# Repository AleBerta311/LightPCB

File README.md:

This PCB uses USB voltage to control a sensor that turns light on when its dark.
The switch and debug pins are used to transfer the code for the microprocessor which controls the sensor and turns on/off the light.

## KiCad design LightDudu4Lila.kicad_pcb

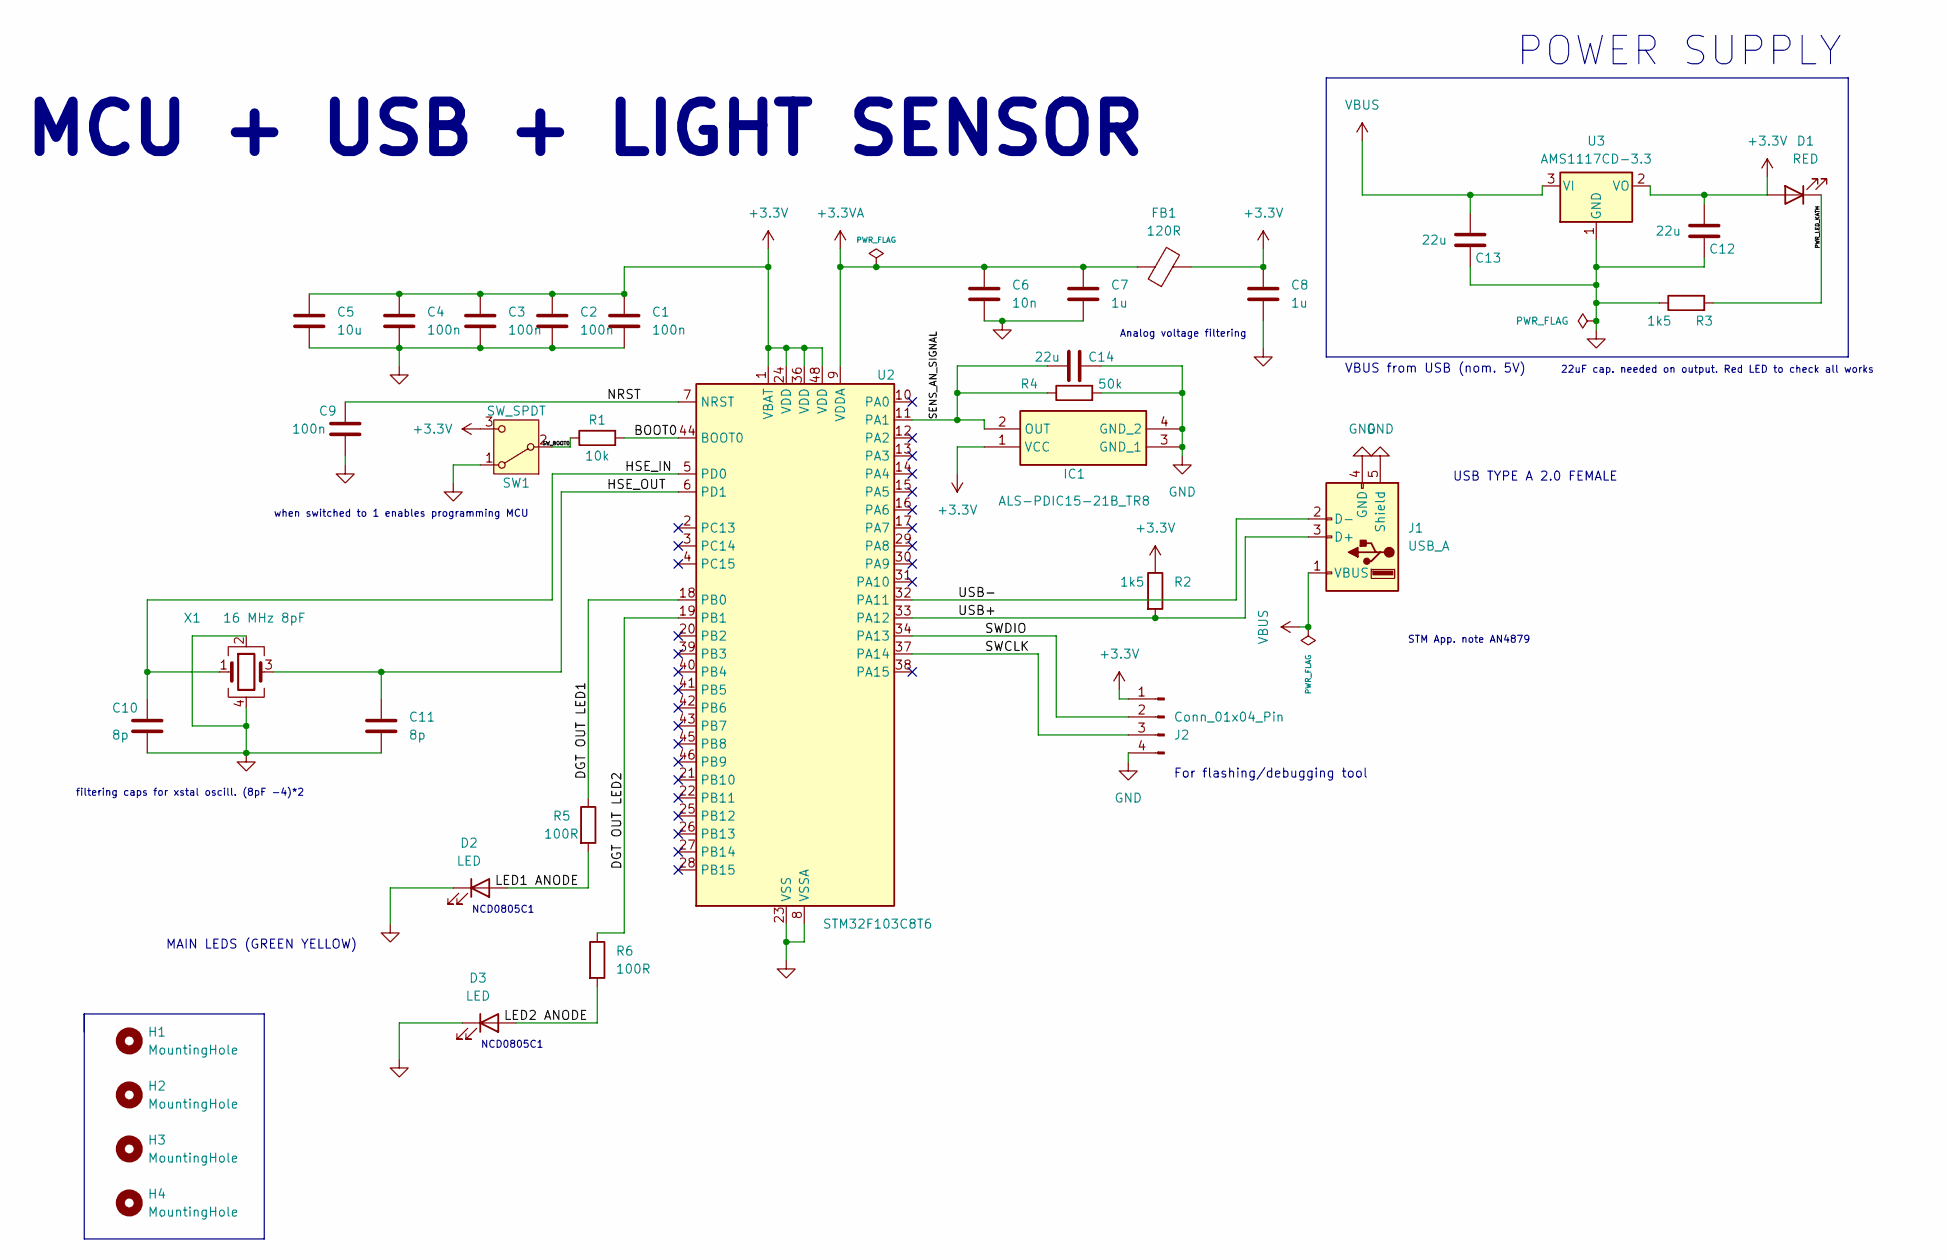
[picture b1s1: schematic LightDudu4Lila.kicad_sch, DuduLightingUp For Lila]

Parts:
C1, C2, C3, C4, C9: 100n; C_0402_1005Metric
C5: 10u; C_0603_1608Metric
C6: 10n; C_0402_1005Metric
C7, C8: 1u; C_0603_1608Metric
C10, C11: 8p; C_0402_1005Metric
C12, C13, C14: 22u; C_0805_2012Metric
D1: RED; LED_0603_1608Metric
D2, D3: LED; LED_0805_2012Metric
FB1: 120R; L_0603_1608Metric
H1, H2, H3, H4: MountingHole; MountingHole_2.2mm_M2
IC1: ALS-PDIC15-21B_TR8; ALSPDIC1521BTR8; Manufacturer_Part_Number ALS-PDIC15-21B/TR8
J1: USB_A; USB_A_Molex_67643_Horizontal
J2: Conn_01x04_Pin; FanPinHeader_1x04_P2.54mm_Vertical
R1: 10k; R_0402_1005Metric
R2, R3: 1k5; R_0402_1005Metric
R4: 50k; R_0805_2012Metric
R5, R6: 100R; R_1206_3216Metric
SW1: SW_SPDT; SW_E-Switch_EG1224_SPDT_Angled
U2: STM32F103C8T6; LQFP-48_7x7mm_P0.5mm
U3: AMS1117CD-3.3; TO-252-3_TabPin2
X1: 16 MHz 8pF; Crystal_SMD_3225-4Pin_3.2x2.5mm

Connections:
+3.3V: C1.1, C2.1, C3.1, C4.1, C5.1, C8.1, C12.1, D1.2 (A), FB1.2, IC1.1 (VCC), J2.1, R2.1, SW1.3 (C), U2.1 (VBAT), U2.24 (VDD), U2.36 (VDD), U2.48 (VDD), U3.2 (VO)
+3.3VA: C6.1, C7.1, FB1.1, U2.9 (VDDA)
/BOOT0: R1.2, U2.44 (BOOT0)
/DGT OUT LED1: R5.1, U2.18 (PB0)
/DGT OUT LED2: R6.1, U2.19 (PB1)
/HSE_IN: C10.1, U2.5 (PD0), X1.1
/HSE_OUT: C11.1, U2.6 (PD1), X1.3
/LED1 ANODE: D2.2 (A), R5.2
/LED2 ANODE: D3.2 (A), R6.2
/NRST: C9.1, U2.7 (NRST)
/PWR_LED_KATH: D1.1 (K), R3.2
/SENS_AN_SIGNAL: C14.1, IC1.2 (OUT), R4.1, U2.11 (PA1)
/SWCLK: J2.3, U2.37 (PA14)
/SWDIO: J2.2, U2.34 (PA13)
/SW_BOOT0: R1.1, SW1.2 (B)
/USB+: J1.3 (D+), R2.2, U2.33 (PA12)
/USB-: J1.2 (D-), U2.32 (PA11)
GND: C1.2, C2.2, C3.2, C4.2, C5.2, C6.2, C7.2, C8.2, C9.2, C10.2, C11.2, C12.2, C13.2, C14.2, D2.1 (K), D3.1 (K), IC1.3 (GND_1), IC1.4 (GND_2), J1.4 (GND), J1.5 (Shield), J2.4, R3.1, R4.2, SW1.1 (A), U2.8 (VSSA), U2.23 (VSS), U2.35 (VSS), U2.47 (VSS), U3.1 (GND), X1.2, X1.4
VBUS: C13.1, J1.1 (VBUS), U3.3 (VI)

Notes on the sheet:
For flashing/debugging tool
VBUS from USB (nom. 5V)
POWER SUPPLY
USB TYPE A 2.0 FEMALE
NCD0805C1
when switched to 1 enables programming MCU
22uF cap. needed on output. Red LED to check all works
filtering caps for xstal oscill. (8pF -4)*2
MCU + USB + LIGHT SENSOR
STM App. note AN4879
MAIN LEDS (GREEN YELLOW)
Analog voltage filtering

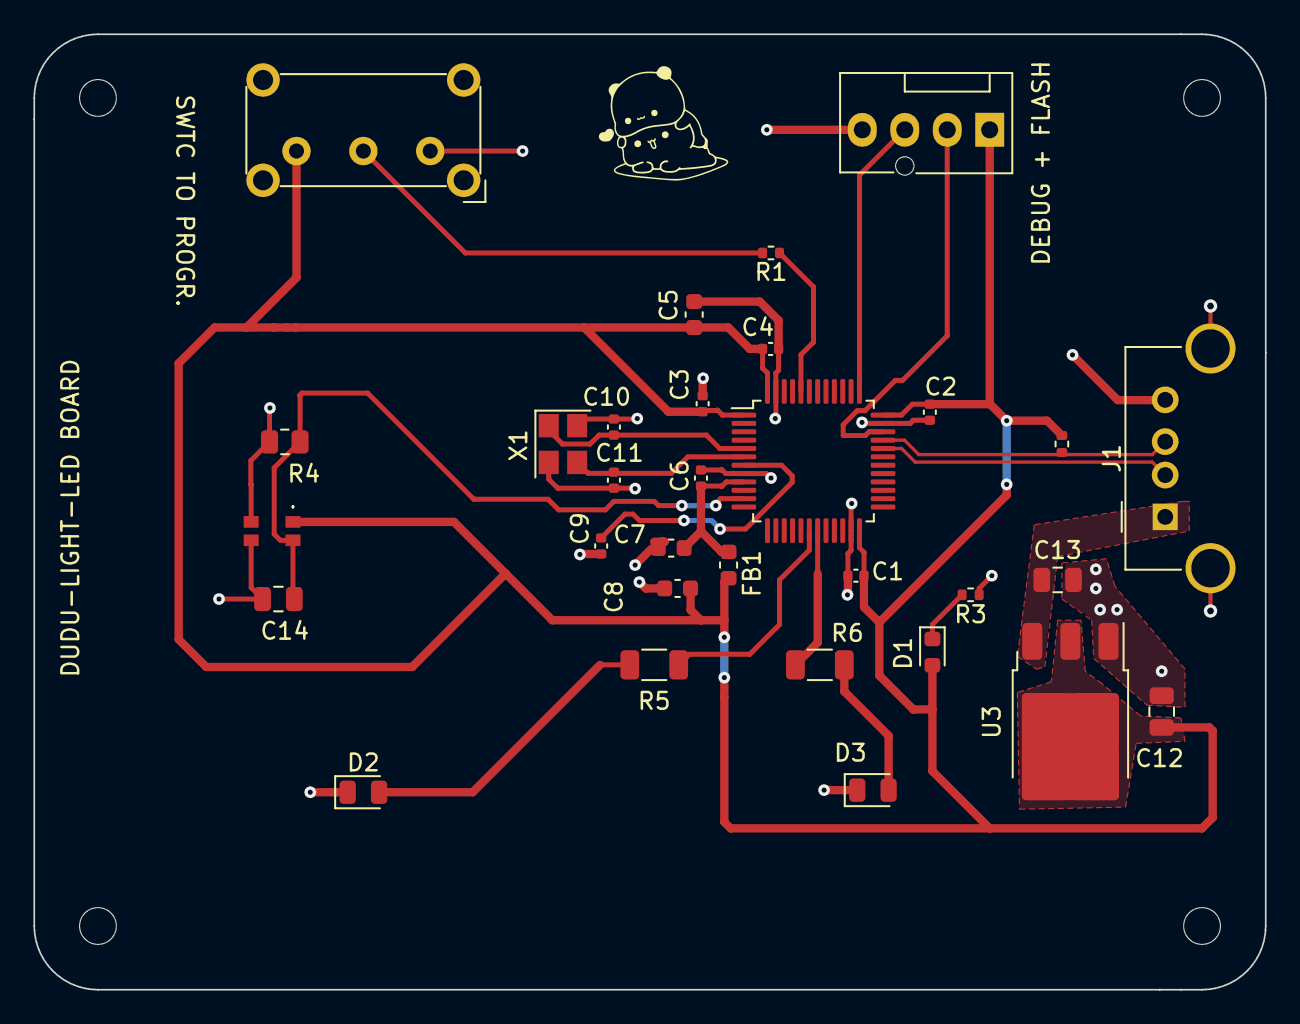
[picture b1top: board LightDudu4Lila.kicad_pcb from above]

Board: 2 copper layers, 73.7 x 57.1 mm, 35 parts (0 on the bottom side), 19 nets.

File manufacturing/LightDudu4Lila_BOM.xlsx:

Designator | Qnty | Comment | Cmp type | Footprint | Description | JLCPCB Part #
C1, C2, C3, C4, C9 | 5 | 100n | C | Capacitor_SMD:C_0402_1005Metric | Unpolarized capacitor | C694490
C5 | 1 | 10u | C | Capacitor_SMD:C_0603_1608Metric | Unpolarized capacitor | C385036
C6 | 1 | 10n | C | Capacitor_SMD:C_0402_1005Metric | Unpolarized capacitor | C342982
C7, C8 | 2 | 1u | C | Capacitor_SMD:C_0603_1608Metric | Unpolarized capacitor | C162280
C10, C11 | 2 | 8p | C | Capacitor_SMD:C_0402_1005Metric | Unpolarized capacitor | C1864375
C12, C13, C14 | 3 | 22u | C | Capacitor_SMD:C_0805_2012Metric | Unpolarized capacitor | C76634
D1 | 1 | red | LED | LED_SMD:LED_0603_1608Metric | Light emitting diode | C2286
D2, D3 | 2 | NCD0805C1 | LED | LED_SMD:LED_0805_2012Metric | Light emitting diode | C84257
FB1 | 1 | 120R @ 1 GHz | FerriteBead | Inductor_SMD:L_0603_1608Metric | Ferrite bead | C127301
IC1 | 1 | ALS-PDIC15-21B_TR8 | ALS-PDIC15-21B_TR8 | 1206 | SENSOR OPT 580NM AMBIENT SMD | C131243
J1 | 1 | 67643-3911 | USB_A | Connector_USB:USB_A_Molex_67643_Horizontal | USB Type A connector | C2765194
J2 | 1 | 01x04 pins connector | Conn_01x04_Pins | Connector:FanPinHeader_1x04_P2.54mm_Vertical | Generic connector, single row, 01x04, script generated
R1 | 1 | 10k | R | Resistor_SMD:R_0402_1005Metric | Resistor | C131361
R2, R3 | 2 | 1k5 | R | Resistor_SMD:R_0402_1005Metric | Resistor | C114759
R4 | 1 | 50k | R | Resistor_SMD:R_0805_2012Metric | Resistor | C2828840
R5, R6 | 2 | 100R | R | Resistor_SMD:R_1206_3216Metric | Resistor | C226677
SW1 | 1 | EG1224 SPDT Angled | SW_SPDT | Button_Switch_THT:SW_E-Switch_EG1224_SPDT_Angled | Switch, single pole double throw | C273395
U2 | 1 | STM32F103C8T6 | STM32F103C8Tx | Package_QFP:LQFP-48_7x7mm_P0.5mm | STMicroelectronics Arm Cortex-M3 MCU, 64KB flash, 20KB RAM, 72 MHz, 2.0-3.6V, 3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 | C8734
U3 | 1 | AMS1117CD-3.3 | AMS1117CD-3.3 | Package_TO_SOT_SMD:TO-252-3_TabPin2 | 1A Low Dropout regulator, positive, 3.3V fixed output, TO-252 | C841796
X1 | 1 | 16 MHz 8pF | Crystal_GND24 | Crystal:Crystal_SMD_3225-4Pin_3.2x2.5mm | Four pin crystal, GND on pins 2 and 4 | C5360874

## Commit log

2025-01-15 Files uploaded
2025-01-15 Testing Git config
2025-01-15 Project header image
